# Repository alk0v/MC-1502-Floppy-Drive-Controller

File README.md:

# Floppy Drive Controller for Electronika MC-1502 computer
Replica of Floppy Drive Controller for Electronica MC-1502 Computer
Based on the original PCB, Zorel and Val_DP remakes.
The original design was developed in Jun 1991 by Kurapin (design), Tokar (checked), Safat (tested), and Teslenko (approved).

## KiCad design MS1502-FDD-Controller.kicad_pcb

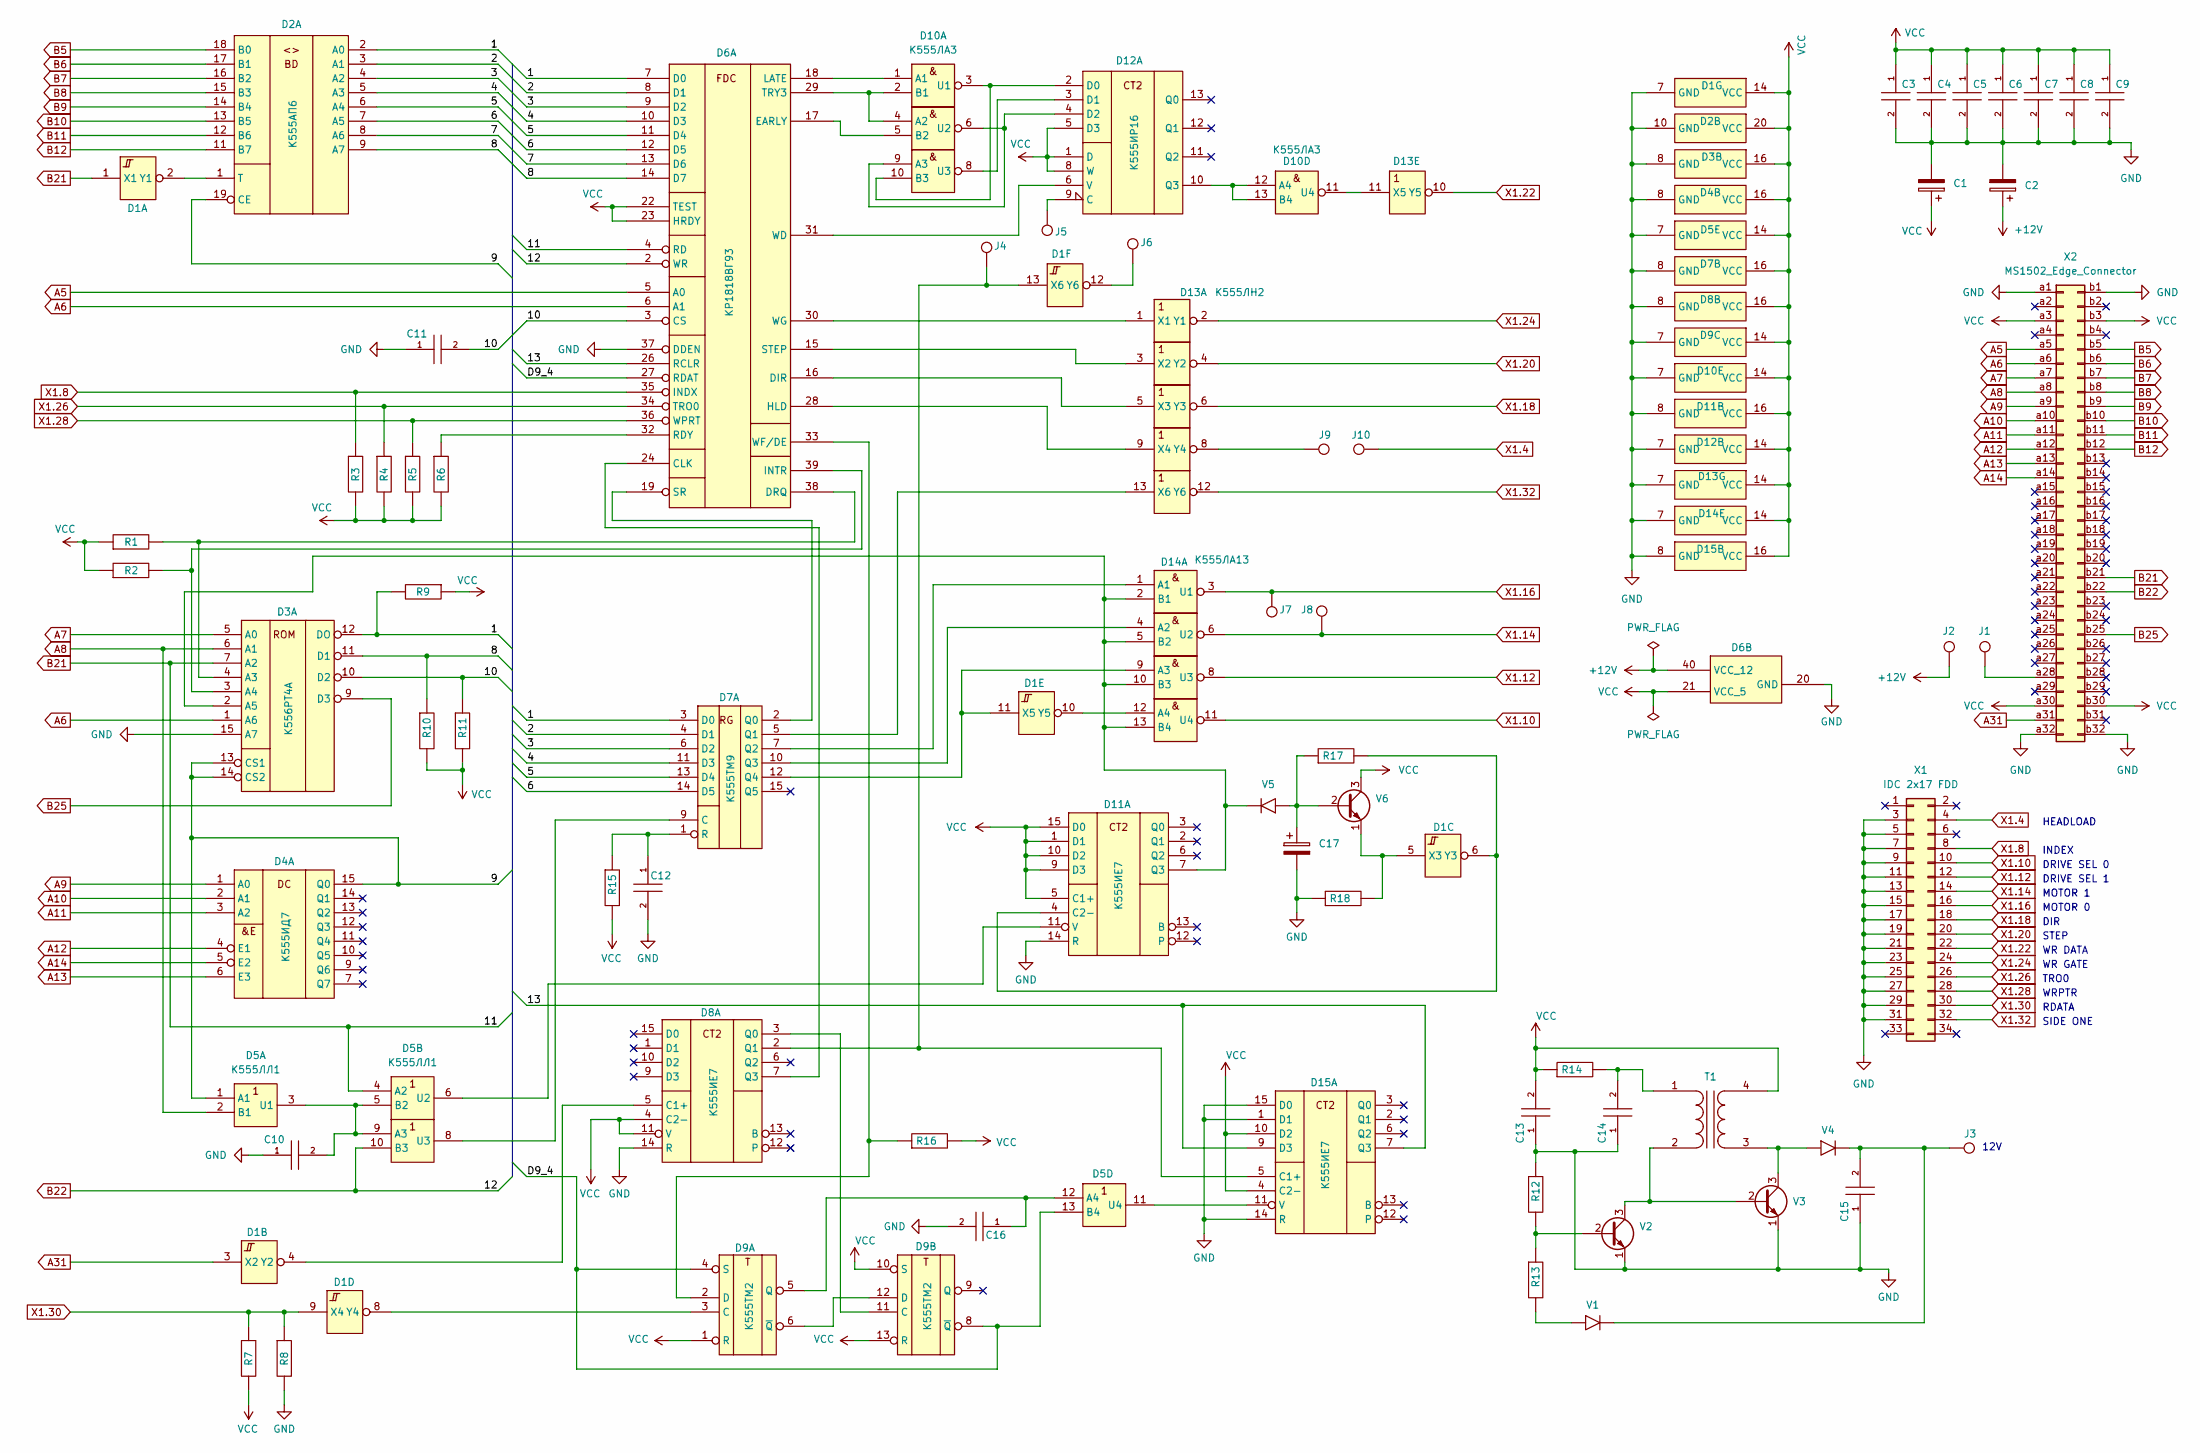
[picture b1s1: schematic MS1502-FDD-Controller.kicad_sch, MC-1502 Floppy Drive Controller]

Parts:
C1: 47uFx16V; CP_Radial_D5.0mm_P2.50mm
C2, C17: 47uFx16V; CP_Radial_D5.0mm_P2.00mm
C3, C6, C12: 150 nF; cap_4mm
C4, C5, C7, C8, C9, C13, C14, C15: 150 nF; cap_5mm
C10, C11, C16: 100 pF; cap_5mm
D1: К555ТЛ2; 201.14-8
D2: К555АП6; 2140.20-1
D3: К556РТ4А; 201.16.5
D4: К555ИД7; 201.16.5
D5: К555ЛЛ1; 201.14-8
D6: КР1818ВГ93; 2123.40-6
D7: К555ТМ9; 201.16.5
D8, D11, D15: К555ИЕ7; 201.16.5
D9: К555ТМ2; 201.14-8
D10: К555ЛА3; 201.14-8
D12: К555ИР16; 201.14-8
D13: К555ЛН2; 201.14-8
D14: К555ЛА13; 201.14-8
J1, J2, J3, J4, J5, J6, J7, J8, J9, J10: round_pin
R1, R2, R10, R16, R17: 10 kOhm; 2pin_100
R3, R4, R5, R6, R7, R11: 560 Ohm; 2pin_100
R8: 1,2 kOhm; 2pin_100
R9: 10 kOhm; 2pin_0875
R12: 2 kOhm; 2pin_100
R13: 1 kOhm; 2pin_100
R14, R18: 820 Ohm; 2pin_100
R15: 4,7 kOhm; 2pin_100
T1: Transformer_1P_1S; transformer_1
V1: КС211Ж; 2pin_150_polar
V2, V6: КТ315Г; VT_5mm
V3: КТ817Г; VT_TO126
V4, V5: КД522Б; 2pin_150_polar
X1: IDC 2x17 FDD; IDC-Header_2x17_P2.54mm_Vertical
X2: MS1502_Edge_Connector; MS1502_edge

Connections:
+12V: C2.1, D6.40 (VCC_12), J2.1
/1: D2.2 (A0), D3.12 (DO), D6.7 (D0), D7.3 (D0), R9.2
/2: D2.3 (A1), D6.8 (D1), D7.4 (D1)
/3: D2.4 (A2), D6.9 (D2), D7.6 (D2)
/4: D2.5 (A3), D6.10 (D3), D7.11 (D3)
/5: D2.6 (A4), D6.11 (D4), D7.13 (D4)
/6: D2.7 (A5), D6.12 (D5), D7.14 (D5)
/7: D2.8 (A6), D6.13 (D6)
/8: D2.9 (A7), D3.11 (D1), D6.14 (D7), R10.1
/9: D2.19 (CE), D3.13 (CS1), D3.14 (CS2), D4.15 (Q0), D5.1 (A1)
/10: C11.2, D3.10 (D2), D6.3 (CS), R11.1
/13: D6.26 (RCLR), D15.7 (Q3), D15.9 (D3)
/D9_4: D5.13 (B4), D6.27 (RDAT), D9.4 (S), D9.8 (~Q)
A5: D6.5 (A0), X2.a5
A6: D3.1 (A6), D6.6 (A1), X2.a6
A7: D3.5 (A0), X2.a7
A8: D3.6 (A1), D5.2 (B1), X2.a8
A9: D4.1 (A0), X2.a9
A10: D4.2 (A1), X2.a10
A11: D4.3 (A2), X2.a11
A12: D4.4 (E1), X2.a12
A13: D4.6 (E3), X2.a13
A14: D4.5 (E2), X2.a14
A31: D1.3 (X2), X2.a31
B5: D2.18 (B0), X2.b5
B6: D2.17 (B1), X2.b6
B7: D2.16 (B2), X2.b7
B8: D2.15 (B3), X2.b8
B9: D2.14 (B4), X2.b9
B10: D2.13 (B5), X2.b10
B11: D2.12 (B6), X2.b11
B12: D2.11 (B7), X2.b12
B21: D1.1 (X1), D3.7 (A2), D5.4 (A2), D6.4 (RD), X2.b21
B22: D5.10 (B3), D6.2 (WR), X2.b22
B25: D3.9 (D3), X2.b25
GND: C1.2, C2.2, C3.2, C4.2, C5.2, C6.2, C7.2, C8.2, C9.2, C10.1, C11.1, C12.2, C13.1, C14.1, C15.1, C16.2, C17.2, D1.7 (GND), D2.10 (GND), D3.8 (GND), D3.15 (A7), D4.8 (GND), D5.7 (GND), D6.20 (GND), D6.37 (DDEN), D7.8 (GND), D8.8 (GND), D8.14 (R), D9.7 (GND), D10.7 (GND), D11.8 (GND), D11.14 (R), D12.7 (GND), D13.7 (GND), D14.7 (GND), D15.1 (D1), D15.8 (GND), D15.14 (R), D15.15 (D0), R8.2, R12.1, R18.1, V2.1 (E), V3.1 (E), X1.3, X1.5, X1.7, X1.9, X1.11, X1.13, X1.15, X1.17, X1.19, X1.21, X1.23, X1.25, X1.27, X1.29, X1.31, X2.a1, X2.a32, X2.b1, X2.b32
unnamed: C15.2, J3.1, V1.2, V4.2
unnamed: D1.2 (Y1), D2.1 (T)
unnamed: D1.4 (Y2), D8.5 (C1+)
unnamed: D1.5 (X3), R18.2, V6.1 (E)
unnamed: D1.8 (Y4), D9.3 (C)
unnamed: D1.12 (Y6), J6.1
unnamed: D3.4 (A3), D6.38 (DRQ), R1.2
unnamed: D3.3 (A4), D6.39 (INTR), R2.2
unnamed: C10.2, D5.3 (U1), D5.5 (B2), D5.9 (A3)
unnamed: D5.8 (U3), D7.9 (C)
unnamed: C16.1, D5.12 (A4), D9.5 (Q)
unnamed: D6.24 (CLK), D8.7 (Q3)
unnamed: D6.32 (RDY), R6.1
unnamed: D6.19 (SR), D7.2 (Q0)
unnamed: D6.33 (WF/DE), D9.2 (D), R16.1
unnamed: C12.1, D7.1 (R), R15.1
unnamed: D8.3 (Q0), D9.11 (C)
unnamed: D9.6 (~Q), D9.12 (D)
unnamed: D6.18 (LATE), D10.1 (A1)
unnamed: D6.29 (TRY3), D10.2 (B1), D10.4 (A2)
unnamed: D10.3 (U1), D10.10 (B3), D12.2 (D0)
unnamed: D6.17 (EARLY), D10.5 (B2)
unnamed: D10.6 (U2), D10.9 (A3), D12.4 (D2)
unnamed: D10.8 (U3), D12.3 (D1)
unnamed: D10.12 (A4), D10.13 (B4), D12.10 (Q3)
unnamed: D10.11 (U4), D13.11 (X5)
unnamed: D1.6 (Y3), D11.4 (C2-), R17.2
unnamed: D3.2 (A5), D11.7 (Q3), D14.2 (B1), D14.5 (B2), D14.10 (B3), D14.13 (B4), V5.2
unnamed: D5.6 (U2), D11.11 (V)
unnamed: D12.9 (C), J5.1
unnamed: D6.31 (WD), D12.6 (V)
unnamed: D6.30 (WG), D13.1 (X1)
unnamed: D6.15 (STEP), D13.3 (X2)
unnamed: D6.16 (DIR), D13.5 (X3)
unnamed: D6.28 (HLD), D13.9 (X4)
unnamed: D13.8 (Y4), J9.1
unnamed: D7.5 (Q1), D13.13 (X6)
unnamed: D7.7 (Q2), D14.1 (A1)
unnamed: D7.10 (Q3), D14.4 (A2)
unnamed: D1.11 (X5), D7.12 (Q4), D14.9 (A3)
unnamed: D1.10 (Y5), D14.12 (A4)
unnamed: D1.13 (X6), D8.2 (Q1), D15.5 (C1+), J4.1
unnamed: D5.11 (U4), D15.11 (V)
unnamed: R13.2, V1.1
unnamed: C14.2, R14.2, T1.1 (AA)
unnamed: T1.2 (AB), V2.3 (C), V3.2 (B)
unnamed: T1.3 (SA), V3.3 (C), V4.1
unnamed: R12.2, R13.1, V2.2 (B)
unnamed: C17.1, R17.1, V5.1, V6.2 (B)
unnamed: J1.1, X2.a28
VCC: C1.1, C3.1, C4.1, C5.1, C6.1, C7.1, C8.1, C9.1, C13.2, D1.14 (VCC), D2.20 (VCC), D3.16 (VCC), D4.16 (VCC), D5.14 (VCC), D6.21 (VCC_5), D6.22 (TEST), D6.23 (HRDY), D7.16 (VCC), D8.4 (C2-), D8.11 (V), D8.16 (VCC), D9.1 (R), D9.10 (S), D9.13 (R), D9.14 (VCC), D10.14 (VCC), D11.1 (D1), D11.5 (C1+), D11.9 (D3), D11.10 (D2), D11.15 (D0), D11.16 (VCC), D12.1 (D), D12.5 (D3), D12.8 (W), D12.14 (VCC), D13.14 (VCC), D14.14 (VCC), D15.4 (C2-), D15.10 (D2), D15.16 (VCC), R1.1, R2.1, R3.2, R4.2, R5.2, R6.2, R7.2, R9.1, R10.2, R11.2, R14.1, R15.2, R16.2, T1.4 (SB), V6.3 (C), X2.a3, X2.a30, X2.b3, X2.b30
X1.4: J10.1, X1.4
X1.8: D6.35 (INDX), R3.1, X1.8
X1.10: D14.11 (U4), X1.10
X1.12: D14.8 (U3), X1.12
X1.14: D14.6 (U2), J8.1, X1.14
X1.16: D14.3 (U1), J7.1, X1.16
X1.18: D13.6 (Y3), X1.18
X1.20: D13.4 (Y2), X1.20
X1.22: D13.10 (Y5), X1.22
X1.24: D13.2 (Y1), X1.24
X1.26: D6.34 (TRO0), R4.1, X1.26
X1.28: D6.36 (WPRT), R5.1, X1.28
X1.30: D1.9 (X4), R7.1, R8.1, X1.30
X1.32: D13.12 (Y6), X1.32

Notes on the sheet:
HEADLOAD
RDATA
WRPTR
MOTOR 0
WR DATA
DRIVE SEL 0
WR GATE
12V
INDEX
SIDE ONE
DRIVE SEL 1
TRO0
DIR
MOTOR 1
STEP

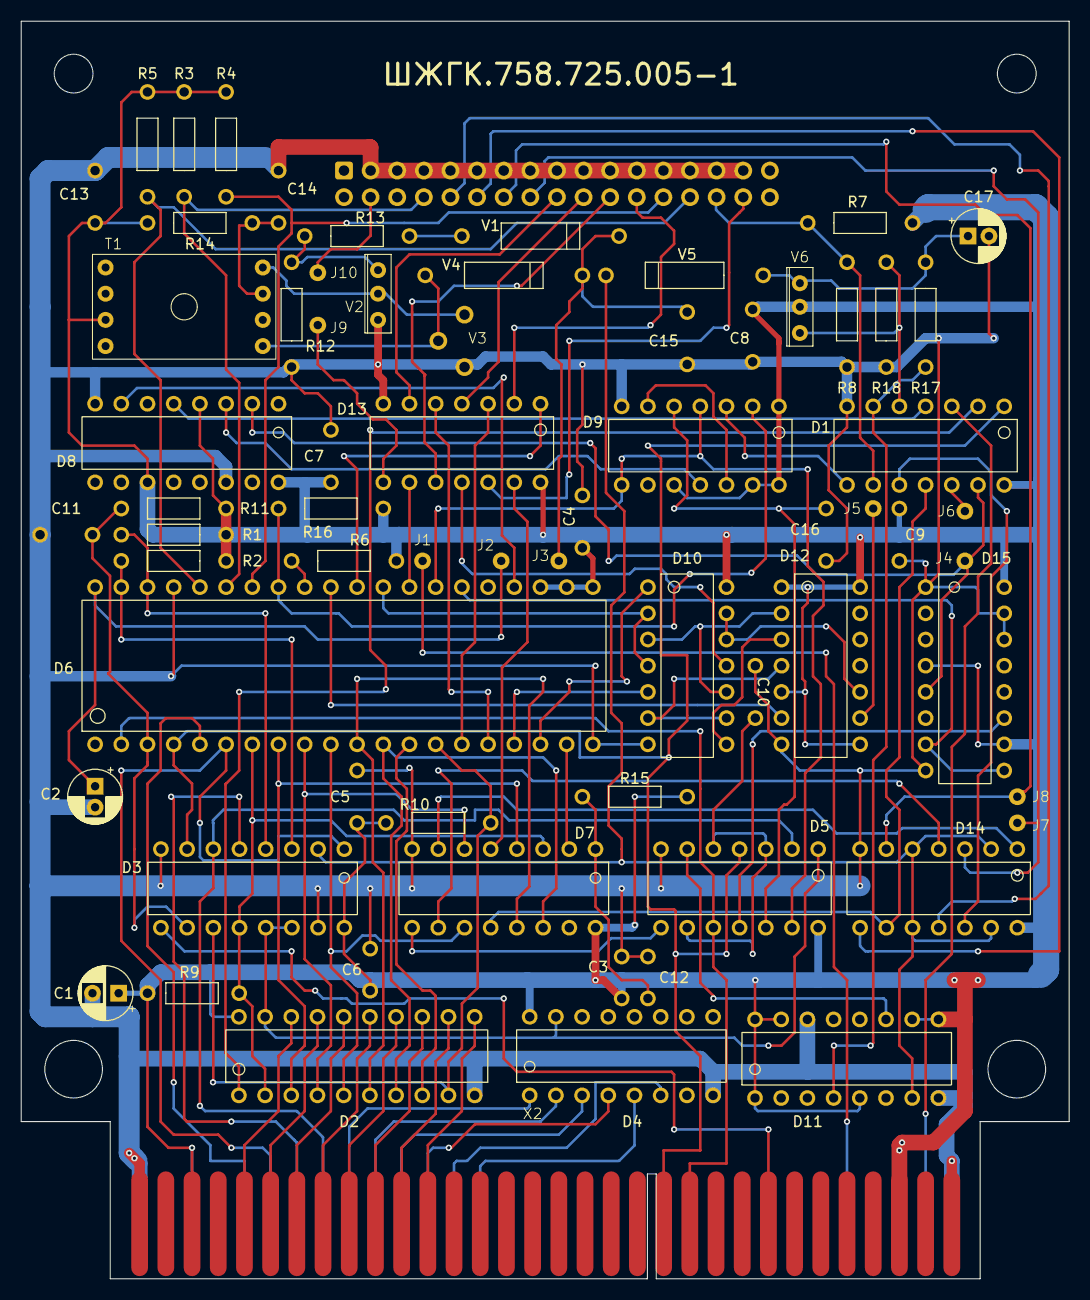
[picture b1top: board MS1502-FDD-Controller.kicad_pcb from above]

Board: 2 copper layers, 100.0 x 120.0 mm, 69 parts (1 on the bottom side), 101 nets.

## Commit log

2025-05-01 v.1.0
2025-05-01 iBom added
